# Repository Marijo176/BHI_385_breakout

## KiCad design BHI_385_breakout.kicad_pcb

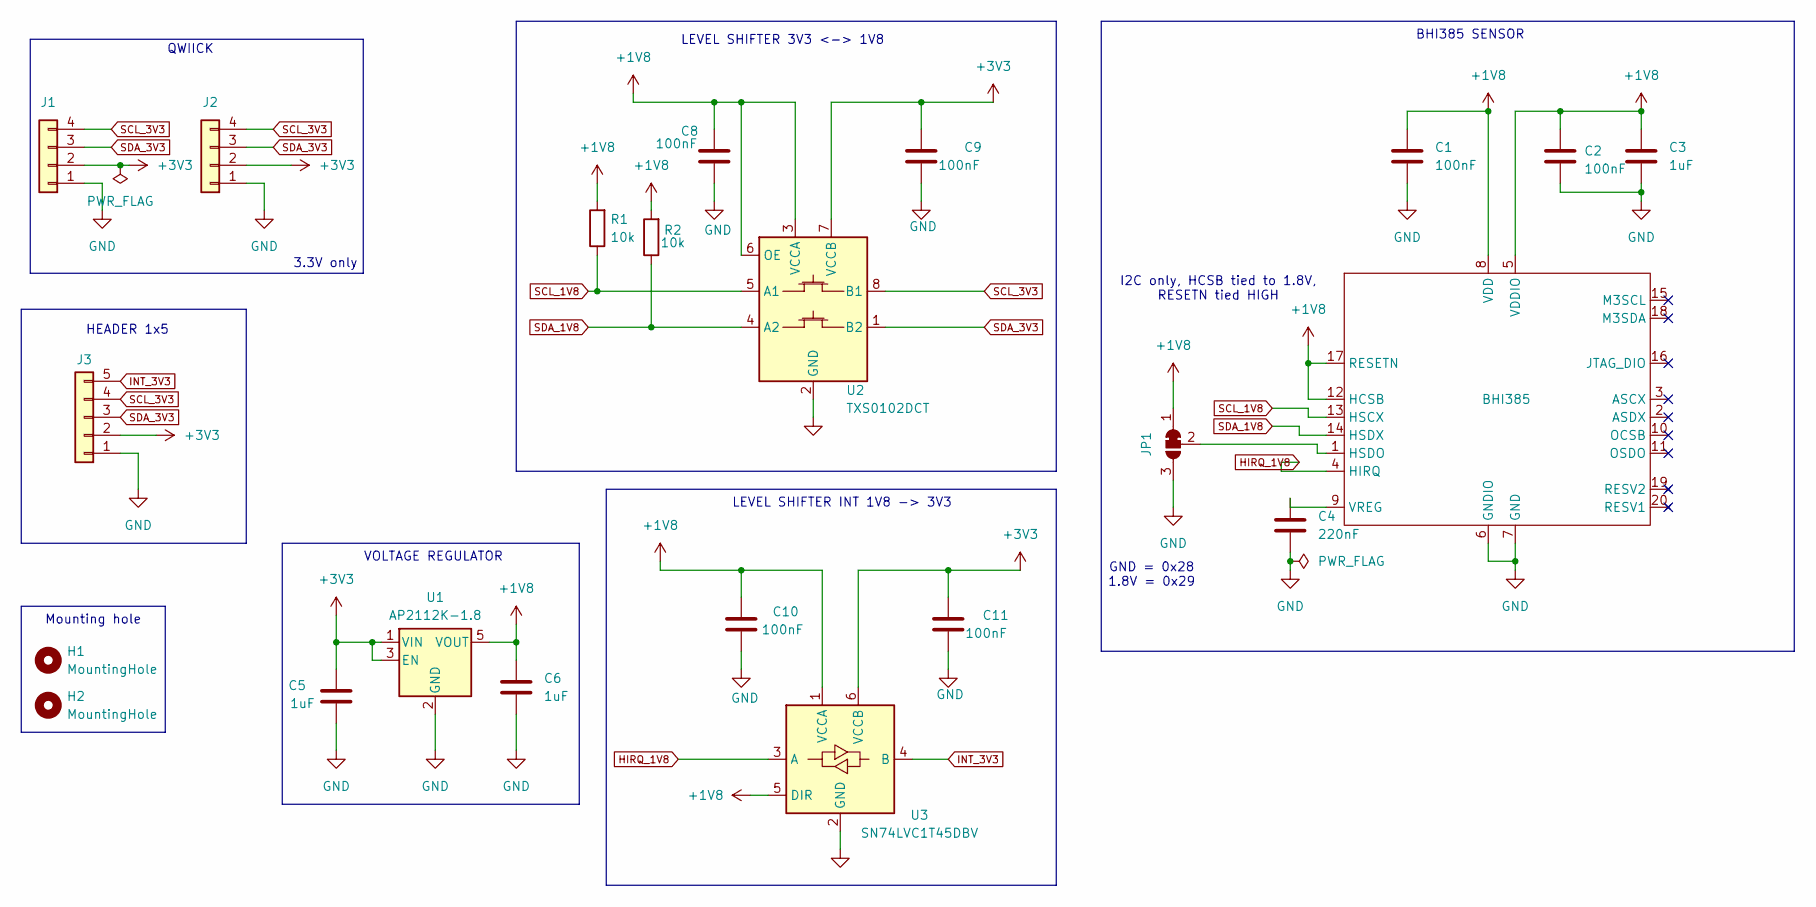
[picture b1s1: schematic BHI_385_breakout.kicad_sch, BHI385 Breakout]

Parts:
C1, C2, C8, C9, C10, C11: 100nF; C_0603_1608Metric
C3, C5, C6: 1uF; C_0603_1608Metric
C4: 220nF; C_0603_1608Metric
H1, H2: MountingHole; MountingHole_2.1mm
J1, J2: SM04B-SRSS-TB; JST_SH_SM04B-SRSS-TB_1x04-1MP_P1.00mm_Horizontal
J3: Conn_01x05; PinHeader_1x05_P2.54mm_Vertical
JP1: SolderJumper_3_Bridged12; SolderJumper-3_P1.3mm_Bridged12_Pad1.0x1.5mm
R1, R2: 10k; R_0603_1608Metric
U1: AP2112K-1.8; SOT-23-5
U2: TXS0102DCT; SSOP-8_2.95x2.8mm_P0.65mm
U3: SN74LVC1T45DBV; SOT-23-6
U4: BHI385; BHI385_LGA-20_2.5x3.0mm

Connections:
+1V8: C1.1, C2.1, C3.1, C6.1, C8.1, C10.1, JP1.1 (A), R1.2, R2.2, U1.5 (VOUT), U2.3 (VCCA), U2.6 (OE), U3.1 (VCCA), U3.5 (DIR), U4.5 (VDDIO), U4.8 (VDD), U4.12 (HCSB), U4.17 (RESETN)
+3V3: C5.1, C9.1, C11.1, J1.2, J2.2, J3.2, U1.1 (VIN), U1.3 (EN), U2.7 (VCCB), U3.6 (VCCB)
GND: C1.2, C2.2, C3.2, C4.2, C5.2, C6.2, C8.2, C9.2, C10.2, C11.2, J1.1, J2.1, J3.1, JP1.3 (B), U1.2 (GND), U2.2 (GND), U3.2 (GND), U4.6 (GNDIO), U4.7 (GND)
HIRQ_1V8: U3.3 (A), U4.4 (HIRQ)
INT_3V3: J3.5, U3.4 (B)
unnamed: JP1.2 (C), U4.1 (HSDO)
unnamed: C4.1, U4.9 (VREG)
SCL_1V8: R1.1, U2.5 (A1), U4.13 (HSCX)
SCL_3V3: J1.4, J2.4, J3.4, U2.8 (B1)
SDA_1V8: R2.1, U2.4 (A2), U4.14 (HSDX)
SDA_3V3: J1.3, J2.3, J3.3, U2.1 (B2)

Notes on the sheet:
I2C only, HCSB tied to 1.8V, RESETN tied HIGH
QWIICK
LEVEL SHIFTER 3V3 <-> 1V8
VOLTAGE REGULATOR
3.3V only
BHI385 SENSOR
LEVEL SHIFTER INT 1V8 -> 3V3
HEADER 1x5
Mounting hole
GND = 0x28 1.8V = 0x29

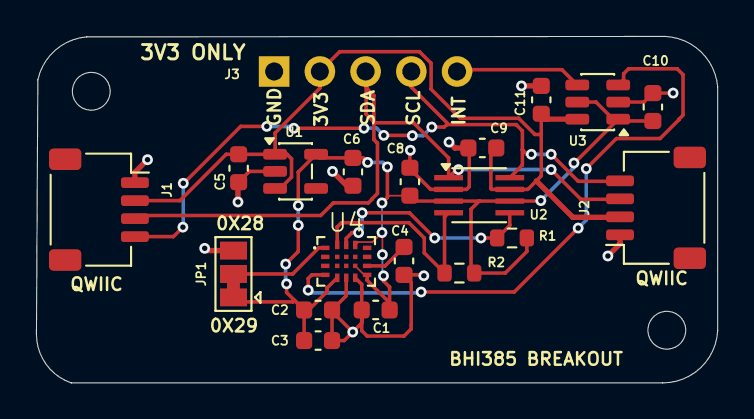
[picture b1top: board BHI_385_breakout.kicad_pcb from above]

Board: 2 copper layers, 37.8 x 19.2 mm, 22 parts (0 on the bottom side), 11 nets.
